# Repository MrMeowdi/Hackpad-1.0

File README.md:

# Hackpad-1.0

This is by far my first project made completely from Tutorials and Guides on YouTube however I made some of the changes by seeking ideas from 2 old hack club events i.e. highway and statis from where I gathered more ideas and easy techniques to do so.

I basically made a hackpad consisting of 8 keys and 1 rotary encoder each having per key RGB and also an OLED screen to view various stats of PC its connected to like resource used etc

I have done the code on VsCode from some of my knowledge and some of ChatGPT

USE ANY KEYCAPS AND ENCODER KNOB OF YOUR CHOICE xd!

## How To Assemble

> Solder all components on the PCB board carefully at its place,  wiring diagram is also shown below  in images section, visit if necessary

> Place the PCB on the desired spot on the Base part of the 3d printed case

> Now close the case by putting some doublesided tape on the poles that get inserted in the spot in the bottom part of the case

## How to Upload Firmware

Now since the assembling part is completed, we need to focus on the firmware part

> Connect the XIAO while a usb-c cable and connect it to your computer

> Use any microcontroller firmware uploading software like "Thonny" or "ArduinoIDE" and install micropython

> Copy and paste the firmware from the main.py or directly download and upload the file in the XIAO

> Upload the 2nd file also named as boot.py enabling Pc stats tramsfer over USB 

### REQUIREMEMTS

These modules are required to install the firmware and make it work 

> psutil
 
> pyserial

## Features And Operations 

**KEY1** — Copy (`Ctrl+C`)  
**KEY2** — Paste (`Ctrl+V`)  
**KEY3** — Undo (`Ctrl+Z`)  
**KEY4** — Cut (`Ctrl+X`)  
**KEY5** — Save (`Ctrl+S`)  
**KEY6** — Switch between open apps (`Alt+Tab`)  
**KEY7** — Go to the start of the current line (`Home`)  
**KEY8** — Open the system task manager (`Ctrl+Shift+Esc`)  
**EC11 single press** — Switch OLED page  
**EC11 double press** — Switch between volume and brightness mode  
**EC11 turn** — Adjust volume or brightness, depending on the selected mode  

## Pricing And BOM

Designator | Component | Selected part / description | Qty on PCB | Purchase pack |
|---|---|---|---:|---|
| MX1–MX8 | Mechanical key switches | [GranVela Outemu red, 3-pin linear, 45 g](https://www.amazon.in/GranVela-Red-Hot-Swappable-Equivalent-Keyboard-20/dp/B073WBY7J3) | 8 | $18.32 / 20 | $7.33 |
| LED1–LED8 | Addressable RGB LEDs | [Lonoa SK6812 MINI-E, 5 V](https://www.ubuy.co.in/productjp/QW0BOLVDC-lonoa-50pcs-sk6812-mini-e-rgb-same-as-ws2812b-sk6812-3228-pixels-led-chip-individually-addressable-full-color-dc5v) | 8 | $2.00 / 50 pcs (user estimate) | $0.32 (8 of 50 LEDs) |
| R1 | Resistor | [Electronic Spices 330 Ω, 1/4 W, ±5%, axial](https://www.amazon.in/Electronic-Spices-Tolerance-Through-Resistors/dp/B0BDG2F7FL) | 1 | $0.84 / 50 | $0.02 |
| U2 | OLED display module | [Robocraze 0.91 in blue, 128×32, I²C/IIC](https://www.amazon.in/dp/B084H9HLCS) | 1 | $2.94 / 1 | $2.94 |
| SW1 | Rotary encoder with push switch | [CentIoT EC11, 5-pin, 20 mm half shaft](https://www.amazon.in/dp/B0888RVZSN) | 1 | $2.63 / 2 | $1.31 |
| U1 | Controller module | [Seeed Studio XIAO RP2040, SKU 102010428](https://www.amazon.in/Microcontroller-Dual-Core-MicroPython-CircuitPython-Interfaces/dp/B09NNVNW7M) | 1 | $16.20 / 1 | $16.20 |
| PCB | Printed circuit board | Macropad PCB | 1 | $14.00 / 1 | $14.00

ESTIMATED TOTAL - `$54.5`

## Images

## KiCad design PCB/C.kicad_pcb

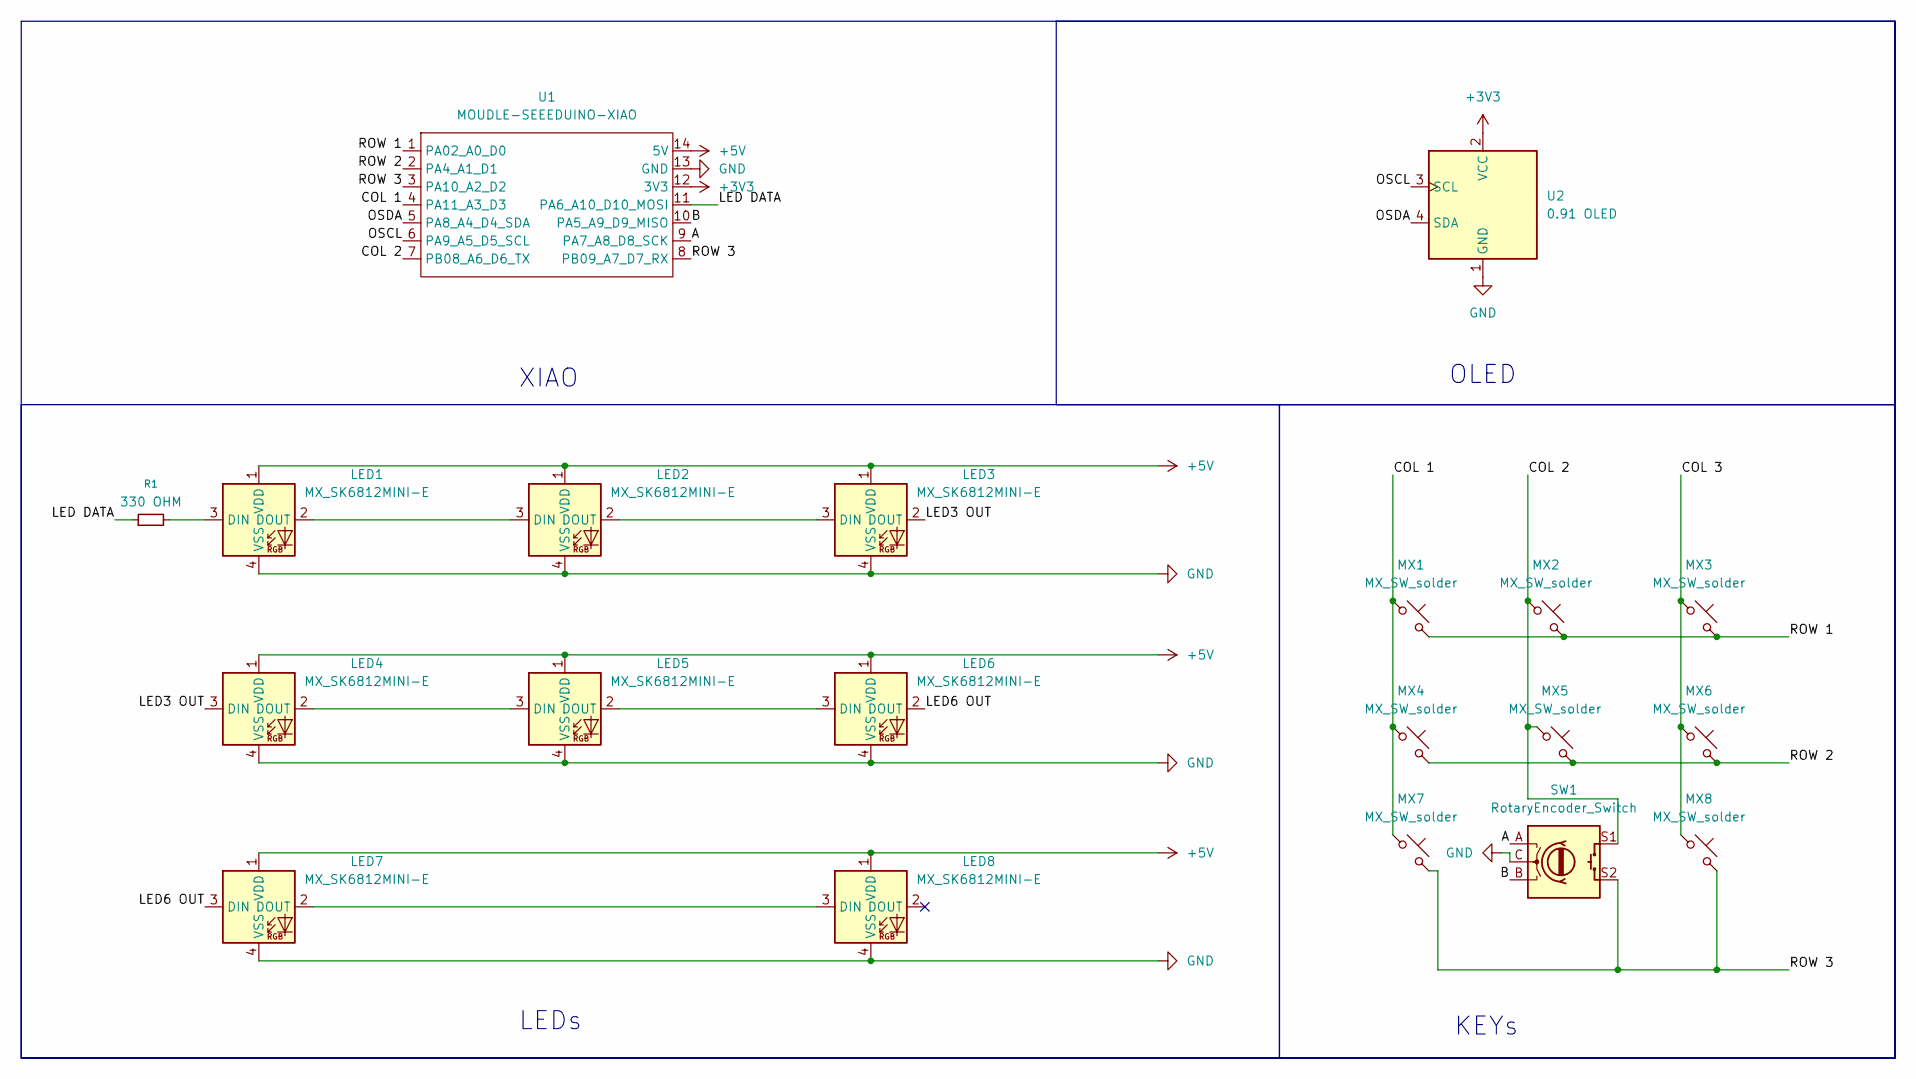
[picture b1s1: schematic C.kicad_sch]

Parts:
LED1, LED2, LED3, LED4, LED5, LED6, LED7, LED8: MX_SK6812MINI-E; LED_MX_6028R
MX1, MX2, MX3, MX4, MX5, MX6, MX7, MX8: MX_SW_solder; SW_MX_1u
R1: 330 OHM; R_Axial_DIN0207_L6.3mm_D2.5mm_P10.16mm_Horizontal
SW1: RotaryEncoder_Switch; RotaryEncoder_Alps_EC11E-Switch_Vertical_H20mm
U1: MOUDLE-SEEEDUINO-XIAO; XIAO-Generic-Hybrid-14P-2.54-21X17.8MM
U2: 0.91 OLED; ER_OLEDM0.91_1x-I2C

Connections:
+3V3: U1.12 (3V3), U2.2 (VCC)
+5V: LED1.1 (VDD), LED2.1 (VDD), LED3.1 (VDD), LED4.1 (VDD), LED5.1 (VDD), LED6.1 (VDD), LED7.1 (VDD), LED8.1 (VDD), U1.14 (5V)
/A: SW1.A, U1.9 (PA7_A8_D8_SCK)
/B: SW1.B, U1.10 (PA5_A9_D9_MISO)
/COL 1: MX1.1, MX4.1, MX7.1, U1.4 (PA11_A3_D3)
/COL 2: MX2.1, MX5.1, SW1.S1, U1.7 (PB08_A6_D6_TX)
/COL 3: MX3.1, MX6.1, MX8.1
/LED3 OUT: LED3.2 (DOUT), LED4.3 (DIN)
/LED6 OUT: LED6.2 (DOUT), LED7.3 (DIN)
/LED DATA: R1.1, U1.11 (PA6_A10_D10_MOSI)
/OSCL: U1.6 (PA9_A5_D5_SCL), U2.3 (SCL)
/OSDA: U1.5 (PA8_A4_D4_SDA), U2.4 (SDA)
/ROW 1: MX1.2, MX2.2, MX3.2, U1.1 (PA02_A0_D0)
/ROW 2: MX4.2, MX5.2, MX6.2, U1.2 (PA4_A1_D1)
/ROW 3: MX7.2, MX8.2, SW1.S2, U1.3 (PA10_A2_D2), U1.8 (PB09_A7_D7_RX)
GND: LED1.4 (VSS), LED2.4 (VSS), LED3.4 (VSS), LED4.4 (VSS), LED5.4 (VSS), LED6.4 (VSS), LED7.4 (VSS), LED8.4 (VSS), SW1.C, U1.13 (GND), U2.1 (GND)
unnamed: LED1.3 (DIN), R1.2
unnamed: LED1.2 (DOUT), LED2.3 (DIN)
unnamed: LED2.2 (DOUT), LED3.3 (DIN)
unnamed: LED4.2 (DOUT), LED5.3 (DIN)
unnamed: LED5.2 (DOUT), LED6.3 (DIN)
unnamed: LED7.2 (DOUT), LED8.3 (DIN)

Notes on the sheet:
XIAO
KEYs
OLED
LEDs

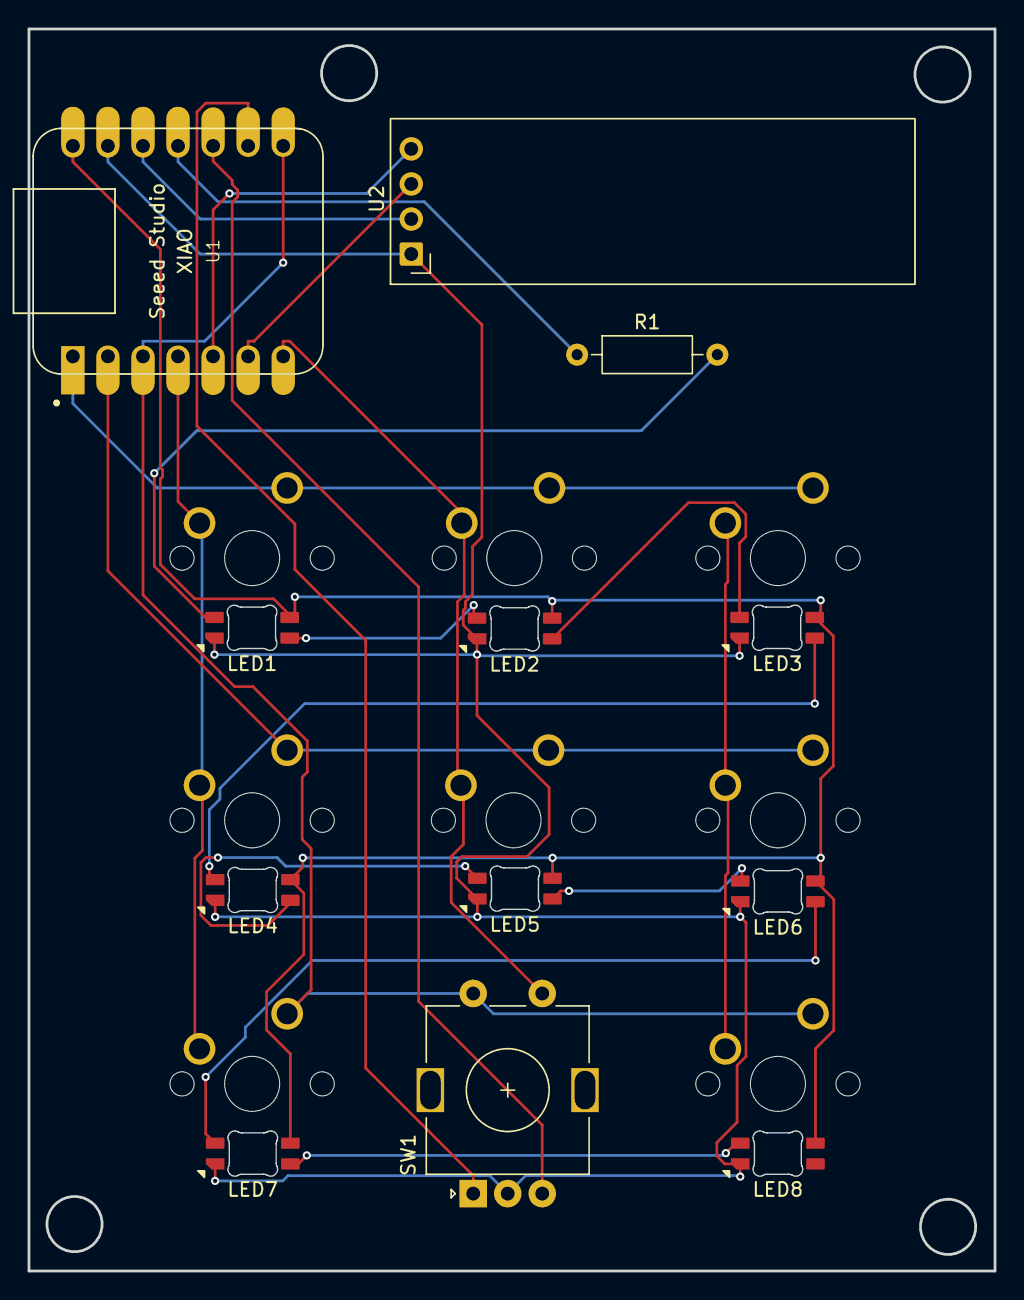
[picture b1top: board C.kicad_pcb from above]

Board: 2 copper layers, 70.0 x 90.0 mm, 20 parts (0 on the bottom side), 22 nets.
